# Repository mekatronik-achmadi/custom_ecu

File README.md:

# Custom Engine Control

This project try to build a custom engine control as flexible as possible, based on STM32 chip series run on RTOS like ChibiOS/RT or FreeRTOS.

## Overview
- Based on STM32F0/F1 series and H11L1 Schmitt Trigger to monitor engine process in real-time and controlling using IRF5xx FET series.
- Provide Serial TTL to USB port for easy realtime monitoring and more custom settings.
- Reading both TPS and Crank tooth for controlling a pair Injectors and a pair Ignition Coils.
- The design currently in very early stage and not for end user usage.

## Crankshaft Position Sensor Alternative

Using Photo Interrupter Sensor and Encoder Wheel with one tooth missing as counter reset.

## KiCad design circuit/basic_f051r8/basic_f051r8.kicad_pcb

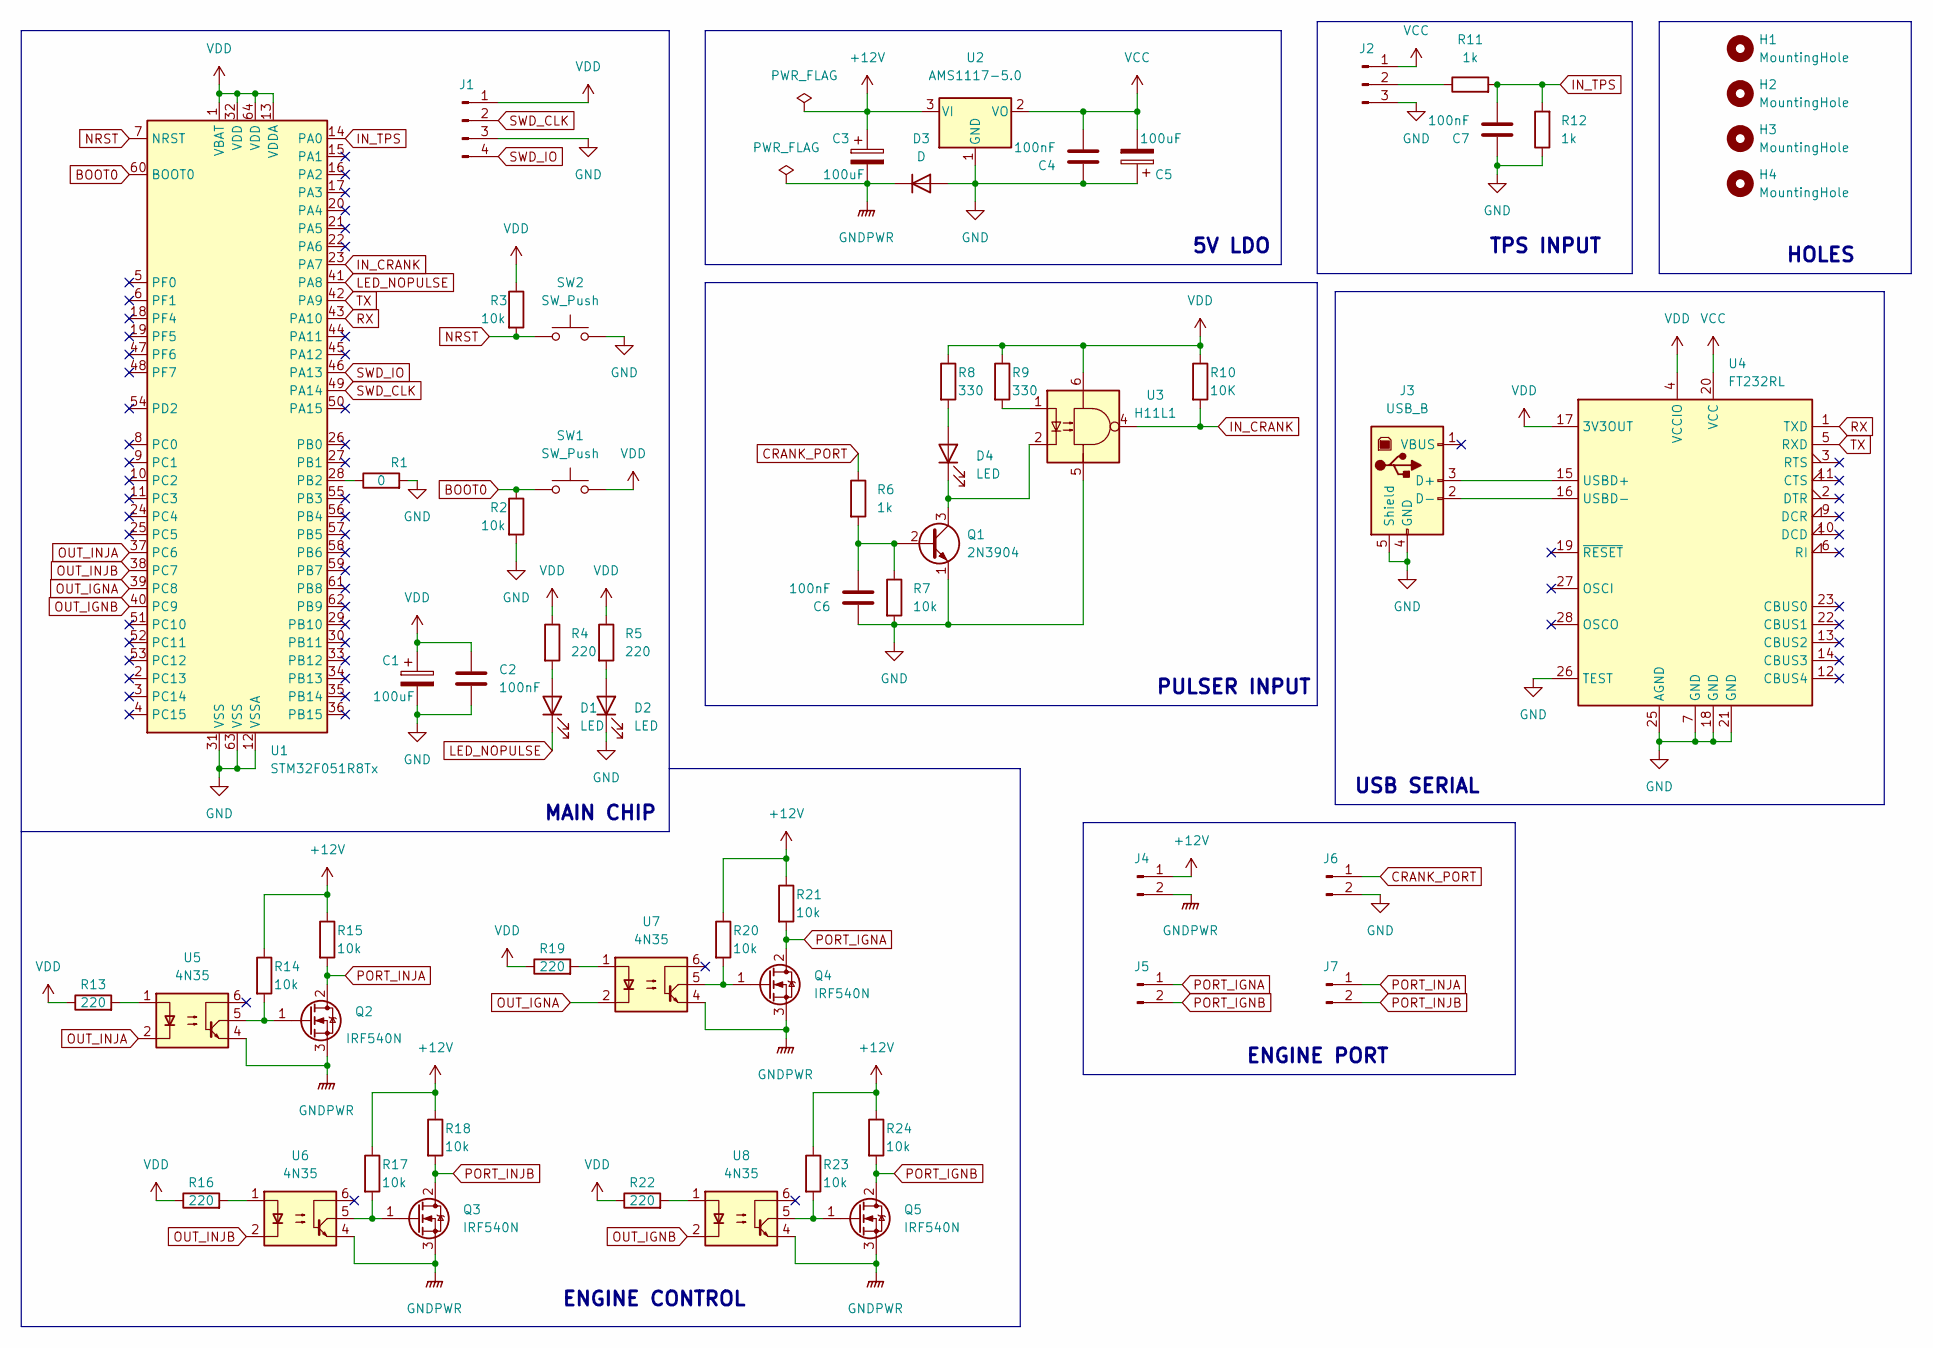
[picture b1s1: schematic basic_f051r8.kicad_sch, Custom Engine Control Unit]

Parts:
C1, C5: 100uF; C_Elec_4x5.4
C2, C4, C6, C7: 100nF; C_0805_2012Metric_Pad1.18x1.45mm_HandSolder
C3: 100uF; C_0805_2012Metric_Pad1.18x1.45mm_HandSolder
D1, D2, D4: LED; LED_0805_2012Metric_Pad1.15x1.40mm_HandSolder
D3: D; D_SMA-SMB_Universal_Handsoldering
H1, H2, H3, H4: MountingHole; MountingHole_2.5mm_Pad
J1: Conn_01x04_Male; PinHeader_1x04_P2.54mm_Vertical
J2: Conn_01x03_Male; TerminalBlock_Altech_AK300-3_P5.00mm
J3: USB_B; USB_B_Lumberg_2411_02_Horizontal
J4, J5, J6, J7: Conn_01x02_Male; TerminalBlock_Altech_AK300-2_P5.00mm
Q1: 2N3904; TO-92_Inline
Q2, Q3, Q4, Q5: IRF540N; TO-220-3_Horizontal_TabUp
R1: 0; R_0805_2012Metric_Pad1.20x1.40mm_HandSolder
R2, R3, R7, R14, R15, R17, R18, R20, R21, R23, R24: 10k; R_0805_2012Metric_Pad1.20x1.40mm_HandSolder
R4, R5, R13, R16, R19, R22: 220; R_0805_2012Metric_Pad1.20x1.40mm_HandSolder
R6, R11, R12: 1k; R_0805_2012Metric_Pad1.20x1.40mm_HandSolder
R8, R9: 330; R_0805_2012Metric_Pad1.20x1.40mm_HandSolder
R10: 10K; R_0805_2012Metric_Pad1.20x1.40mm_HandSolder
SW1, SW2: SW_Push; SW_PUSH_6mm
U1: STM32F051R8Tx; LQFP-64_10x10mm_P0.5mm
U2: AMS1117-5.0; SOT-223-3_TabPin2
U3: H11L1; DIP-6_W7.62mm
U4: FT232RL; SSOP-28_5.3x10.2mm_P0.65mm
U5, U6, U7, U8: 4N35; DIP-6_W7.62mm

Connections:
+12V: C3.1, J4.1, R14.1, R15.1, R17.1, R18.1, R20.1, R21.1, R23.1, R24.1, U2.3 (VI)
BOOT0: R2.1, SW1.1, U1.60 (BOOT0)
CRANK_PORT: J6.1, R6.1
GND: C1.2, C2.2, C4.1, C5.1, C6.1, C7.1, D2.1 (K), D3.2 (A), J1.3, J2.3, J3.4 (GND), J3.5 (Shield), J6.2, Q1.1 (E), R1.2, R2.2, R7.2, R12.1, SW2.2, U1.12 (VSSA), U1.31 (VSS), U1.63 (VSS), U2.1 (GND), U3.5, U4.7 (GND), U4.18 (GND), U4.21 (GND), U4.25 (AGND), U4.26 (TEST)
GNDPWR: C3.2, D3.1 (K), J4.2, Q2.3 (S), Q3.3 (S), Q4.3 (S), Q5.3 (S), U5.4, U6.4, U7.4, U8.4
IN_CRANK: R10.2, U1.23 (PA7), U3.4
IN_TPS: C7.2, R11.2, R12.2, U1.14 (PA0)
LED_NOPULSE: D1.1 (K), U1.41 (PA8)
NRST: R3.2, SW2.1, U1.7 (NRST)
unnamed: C6.2, Q1.2 (B), R6.2, R7.1
unnamed: D1.2 (A), R4.2
unnamed: D2.2 (A), R5.2
unnamed: D4.1 (K), Q1.3 (C), U3.2
unnamed: D4.2 (A), R8.2
unnamed: J2.2, R11.1
unnamed: Q2.1 (G), R14.2, U5.5
unnamed: Q3.1 (G), R17.2, U6.5
unnamed: Q4.1 (G), R20.2, U7.5
unnamed: Q5.1 (G), R23.2, U8.5
unnamed: R1.1, U1.28 (PB2)
unnamed: R9.2, U3.1
unnamed: R13.2, U5.1
unnamed: R16.2, U6.1
unnamed: R19.2, U7.1
unnamed: R22.2, U8.1
unnamed: J3.3 (D+), U4.15 (USBD+)
unnamed: J3.2 (D-), U4.16 (USBD-)
OUT_IGNA: U1.39 (PC8), U7.2
OUT_IGNB: U1.40 (PC9), U8.2
OUT_INJA: U1.37 (PC6), U5.2
OUT_INJB: U1.38 (PC7), U6.2
PORT_IGNA: J5.1, Q4.2 (D), R21.2
PORT_IGNB: J5.2, Q5.2 (D), R24.2
PORT_INJA: J7.1, Q2.2 (D), R15.2
PORT_INJB: J7.2, Q3.2 (D), R18.2
RX: U1.43 (PA10), U4.1 (TXD)
SWD_CLK: J1.2, U1.49 (PA14)
SWD_IO: J1.4, U1.46 (PA13)
TX: U1.42 (PA9), U4.5 (RXD)
VCC: C4.2, C5.2, J2.1, U2.2 (VO), U4.20 (VCC)
VDD: C1.1, C2.1, J1.1, R3.1, R4.1, R5.1, R8.1, R9.1, R10.1, R13.1, R16.1, R19.1, R22.1, SW1.2, U1.1 (VBAT), U1.13 (VDDA), U1.32 (VDD), U1.64 (VDD), U3.6, U4.4 (VCCIO), U4.17 (3V3OUT)

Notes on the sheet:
PULSER INPUT
MAIN CHIP
5V LDO
USB SERIAL
ENGINE PORT
HOLES
TPS INPUT
ENGINE CONTROL

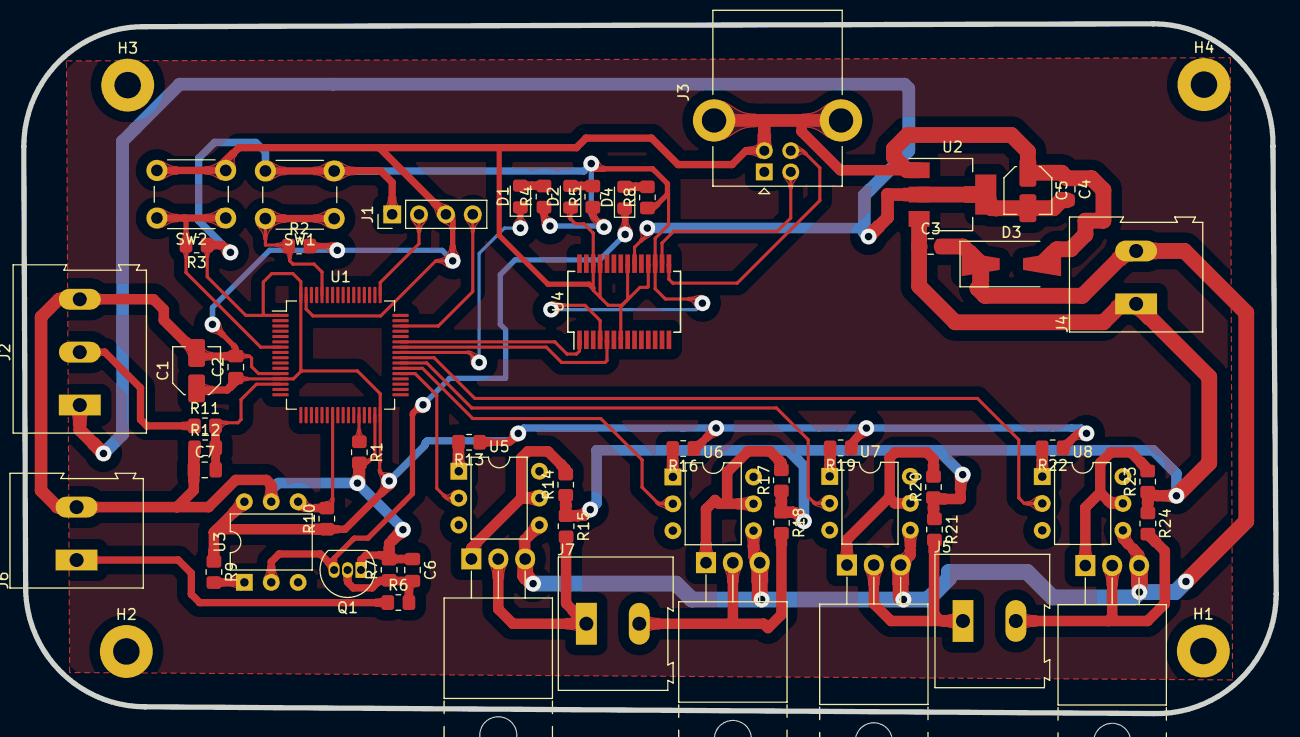
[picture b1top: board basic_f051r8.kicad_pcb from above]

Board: 2 copper layers, 118.4 x 65.2 mm, 61 parts (0 on the bottom side), 41 nets.

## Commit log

2022-12-26 Basic Readme
2022-12-26 Start Circuit
2022-12-26 Schematic
2022-12-26 Schematic Done
2022-12-26 Footprint Assigment
2022-12-26 PCB Layout (No Route)
2022-12-26 PCB 3D components
2022-12-26 PCB Draft Done
2022-12-26 Draft Document
2022-12-26 Use README instead
2022-12-26 Draft Done
2022-12-27 Bill of Material
2022-12-27 Per Unit Price
2022-12-27 Rangkuman Biaya
2022-12-27 Biaya PCB
